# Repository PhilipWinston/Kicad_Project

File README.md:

## 🧾 PCB Design: AC to DC Converter

Designed using **KiCad**, this is a 2-layer PCB layout for an AC to DC converter. The Gerber files have been successfully generated and are ready for fabrication.

### 📁 Gerber Files Included
- **Top & Bottom Copper**: `AC to DC-F_Cu.gbr`, `AC to DC-B_Cu.gbr`
- **Solder Mask**: `AC to DC-F_Mask.gbr`, `AC to DC-B_Mask.gbr`
- **Silkscreen**: `AC to DC-F_Silkscreen.gbr`, `AC to DC-B_Silkscreen.gbr`
- **Solder Paste**: `AC to DC-F_Paste.gbr`, `AC to DC-B_Paste.gbr`
- **Board Outline**: `AC to DC-Edge_Cuts.gbr`
- **Job File**: `AC to DC-job.gbrjob`

### 🛠️ Software Used
- KiCad 8

### 🖼️ How to Preview
To view these files, you can use:
- [KiCad Gerber Viewer](https://www.kicad.org/)
- [Gerber Viewer Online (e.g., Aisler)](https://aisler.net/tools/gerber-viewer)

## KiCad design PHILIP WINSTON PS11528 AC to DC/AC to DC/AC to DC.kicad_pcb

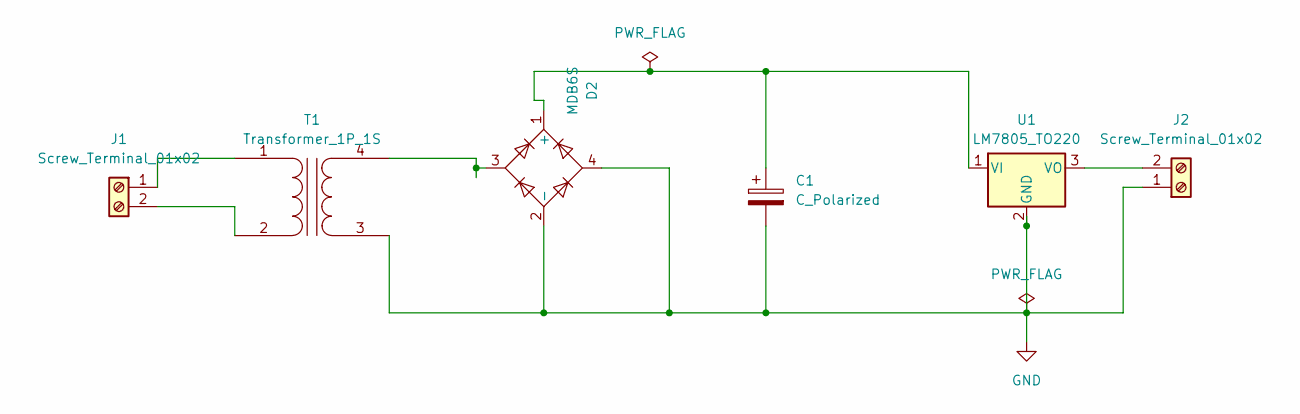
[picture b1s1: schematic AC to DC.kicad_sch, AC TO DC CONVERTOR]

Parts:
C1: C_Polarized; CP_Radial_D10.0mm_P5.00mm_P7.50mm
D2: MDB6S; TSSOP-4_4.4x5mm_P4mm
J1, J2: Screw_Terminal_01x02; TerminalBlock_Altech_AK300-2_P5.00mm
T1: Transformer_1P_1S; Transformer_Zeming_ZMPT101K
U1: LM7805_TO220; TO-220-3_Vertical

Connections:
GND: C1.2, D2.2 (-), D2.4, J2.1, T1.3 (SA), U1.2 (GND)
unnamed: C1.1, D2.1 (+), U1.1 (VI)
unnamed: J1.1, T1.1 (AA)
unnamed: J1.2, T1.2 (AB)
unnamed: J2.2, U1.3 (VO)
unnamed: D2.3, T1.4 (SB)

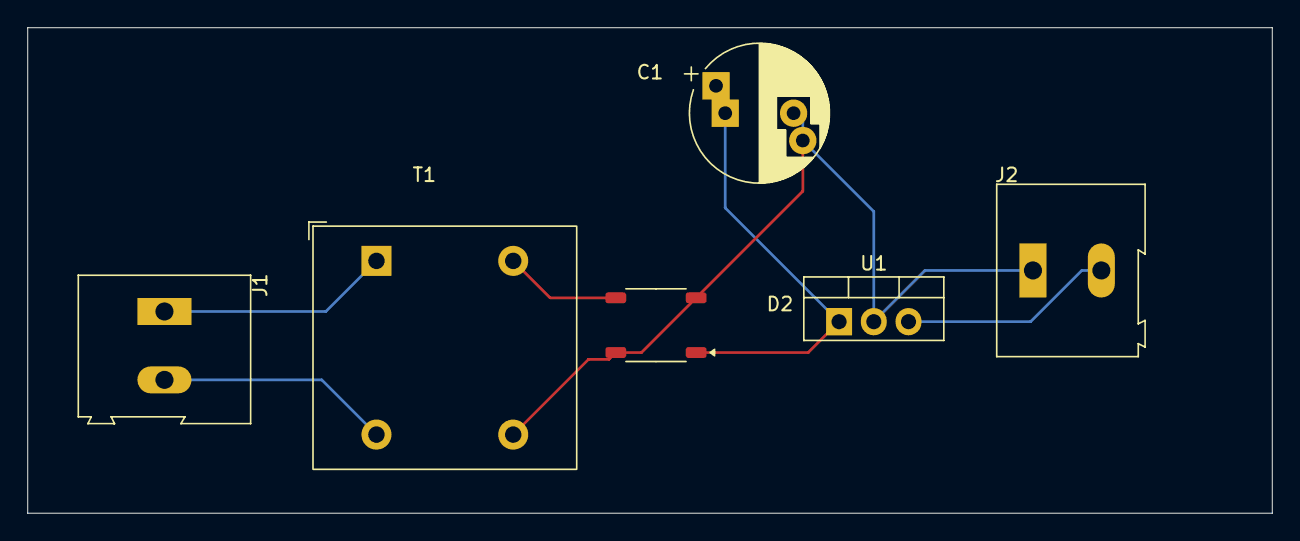
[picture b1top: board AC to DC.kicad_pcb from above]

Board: 2 copper layers, 91.0 x 35.5 mm, 6 parts (0 on the bottom side), 6 nets.

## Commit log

2025-04-17 Added to git
